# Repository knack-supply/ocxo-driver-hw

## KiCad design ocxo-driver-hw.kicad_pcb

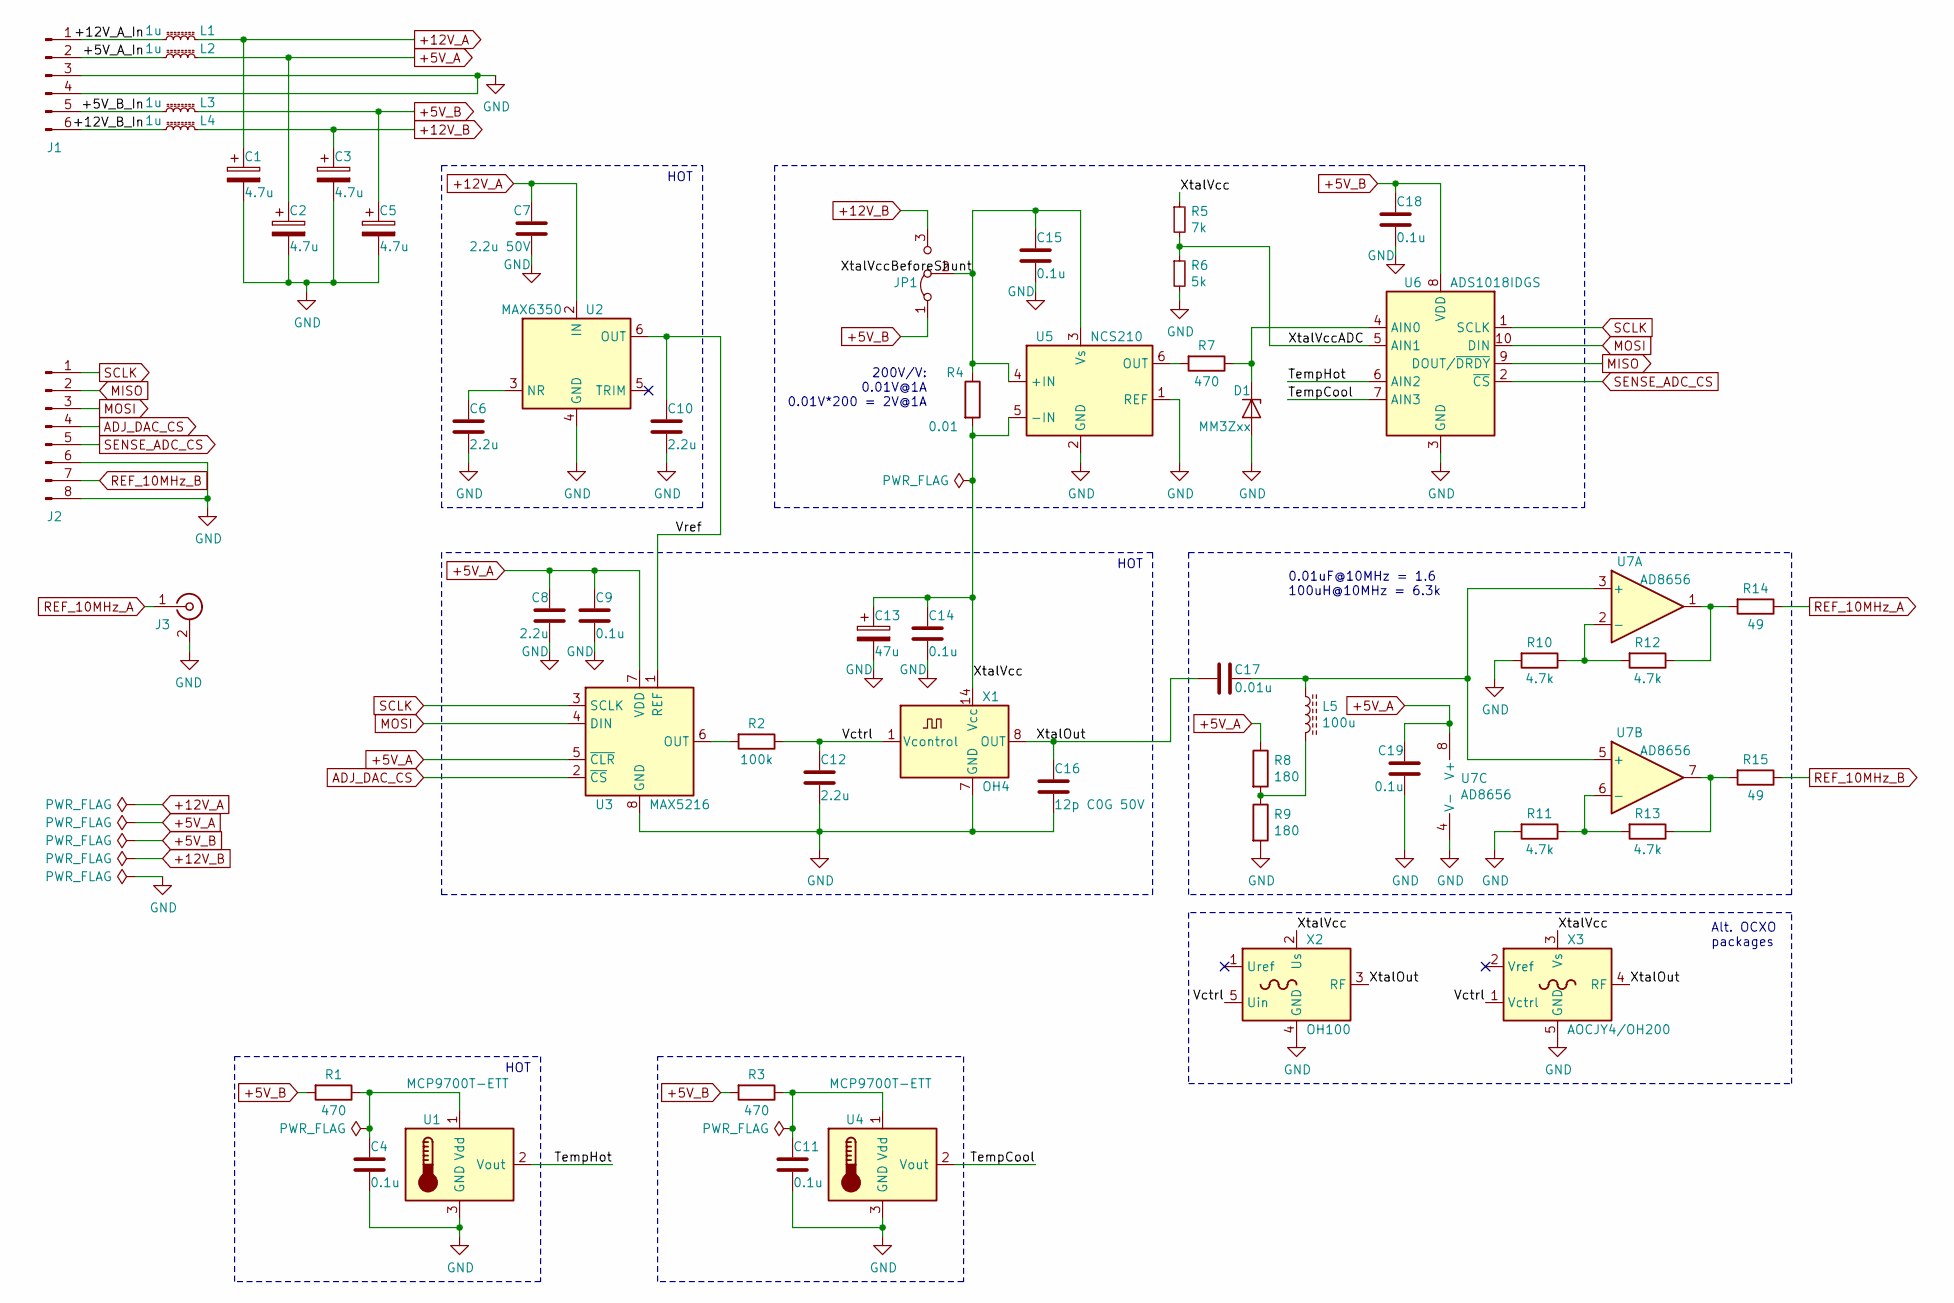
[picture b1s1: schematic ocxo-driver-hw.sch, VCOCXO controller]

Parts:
C1, C2, C3, C5: 4.7u; C_1206_3216Metric_Pad1.42x1.75mm_HandSolder
C4, C9, C11, C14, C15, C18, C19: 0.1u; C_0603_1608Metric_Pad1.05x0.95mm_HandSolder
C6, C8, C10: 2.2u; C_1206_3216Metric_Pad1.42x1.75mm_HandSolder
C7: 2.2u 50V; C_1206_3216Metric_Pad1.42x1.75mm_HandSolder
C12: 2.2u; C_0603_1608Metric_Pad1.05x0.95mm_HandSolder
C13: 47u; C_2816_7142Metric_Pad3.20x4.45mm_HandSolder
C16: 12p C0G 50V; C_0603_1608Metric_Pad1.05x0.95mm_HandSolder
C17: 0.01u; C_0603_1608Metric_Pad1.05x0.95mm_HandSolder
D1: MM3Zxx; D_SOD-123F
J1: Conn_01x06_Male; PinHeader_1x06_P2.54mm_Vertical
J2: Conn_01x08_Male; PinHeader_1x08_P2.54mm_Vertical
J3: Conn_Coaxial; MMCX_Molex_73415-1471_Vertical
JP1: Jumper_3_Bridged12; SolderJumper-3_P2.0mm_Open_TrianglePad1.0x1.5mm
L1, L2, L3, L4: 1u; L_1210_3225Metric_Pad1.42x2.65mm_HandSolder
L5: 100u; L_0805_2012Metric_Pad1.15x1.40mm_HandSolder
R1, R3, R7: 470; R_0603_1608Metric_Pad1.05x0.95mm_HandSolder
R2: 100k; R_0603_1608Metric_Pad1.05x0.95mm_HandSolder
R4: 0.01; R_0603_1608Metric_Pad1.05x0.95mm_HandSolder
R5: 7k; R_0603_1608Metric_Pad1.05x0.95mm_HandSolder
R6: 5k; R_0603_1608Metric_Pad1.05x0.95mm_HandSolder
R8, R9: 180; R_0603_1608Metric_Pad1.05x0.95mm_HandSolder
R10, R11, R12, R13: 4.7k; R_0603_1608Metric_Pad1.05x0.95mm_HandSolder
R14, R15: 49; R_0603_1608Metric_Pad1.05x0.95mm_HandSolder
U1, U4: MCP9700T-ETT; SOT-23
U2: MAX6350; SOIC-8_3.9x4.9mm_P1.27mm
U3: MAX5216; MSOP-8_3x3mm_P0.65mm
U5: NCS210; SOT-363_SC-70-6
U6: ADS1018IDGS; VSSOP-10_3x3mm_P0.5mm
U7: AD8656; SOIC-8_3.9x4.9mm_P1.27mm
X1: OH4; Oscillator_DIP-14
X2: OH100; Oscillator_OCXO_Morion_MV317
X3: AOCJY4/OH200; Oscillator_OCXO_Abracon_AOCJY4

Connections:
+5V_A: C2.1, C8.1, C9.1, C19.1, L2.2, R8.1, U3.5 (~CLR), U3.7 (VDD), U7.8 (V+)
+5V_B: C5.1, C18.1, JP1.1 (A), L3.2, R1.2, R3.2, U6.8 (VDD)
+12V_A: C1.1, C7.1, L1.2, U2.2 (IN)
+12V_B: C3.1, JP1.3 (B), L4.2
/+5V_A_In: J1.2, L2.1
/+5V_B_In: J1.5, L3.1
/+12V_A_In: J1.1, L1.1
/+12V_B_In: J1.6, L4.1
/TempCool: U4.2 (Vout), U6.7 (AIN3)
/TempHot: U1.2 (Vout), U6.6 (AIN2)
/Vctrl: C12.1, R2.1, X1.1 (Vcontrol), X2.5 (Uin), X3.1 (Vctrl)
/Vref: C10.1, U2.6 (OUT), U3.1 (REF)
/XtalOut: C16.1, C17.2, X1.8 (OUT), X2.3 (RF), X3.4 (RF)
/XtalVcc: C13.1, C14.1, R4.2, R5.1, U5.5 (-IN), X1.14 (Vcc), X2.2 (Us), X3.3 (Vs)
/XtalVccADC: R5.2, R6.1, U6.5 (AIN1)
/XtalVccBeforeShunt: C15.1, JP1.2 (C), R4.1, U5.3 (Vs), U5.4 (+IN)
ADJ_DAC_CS: J2.4, U3.2 (~CS)
GND: C1.2, C2.2, C3.2, C4.2, C5.2, C6.2, C7.2, C8.2, C9.2, C10.2, C11.2, C12.2, C13.2, C14.2, C15.2, C16.2, C18.2, C19.2, D1.2 (A), J1.3, J1.4, J2.6, J2.8, J3.2 (Ext), R6.2, R9.2, R10.2, R11.2, U1.3 (GND), U2.4 (GND), U3.8 (GND), U4.3 (GND), U5.1 (REF), U5.2 (GND), U6.3 (GND), U7.4 (V-), X1.7 (GND), X2.4 (GND), X3.5 (GND)
MISO: J2.2, U6.9 (DOUT/~DRDY)
MOSI: J2.3, U3.4 (DIN), U6.10 (DIN)
unnamed: C4.1, R1.1, U1.1 (Vdd)
unnamed: C6.1, U2.3 (NR)
unnamed: C11.1, R3.1, U4.1 (Vdd)
unnamed: C17.1, L5.1, U7.3 (+), U7.5 (+)
unnamed: D1.1 (K), R7.1, U6.4 (AIN0)
unnamed: L5.2, R8.2, R9.1
unnamed: R2.2, U3.6 (OUT)
unnamed: R7.2, U5.6 (OUT)
unnamed: R10.1, R12.2, U7.2 (-)
unnamed: R11.1, R13.2, U7.6 (-)
unnamed: R12.1, R14.2, U7.1
unnamed: R13.1, R15.2, U7.7
REF_10MHz_A: J3.1 (In), R14.1
REF_10MHz_B: J2.7, R15.1
SCLK: J2.1, U3.3 (SCLK), U6.1 (SCLK)
SENSE_ADC_CS: J2.5, U6.2 (~CS)

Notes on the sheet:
200V/V: 0.01V@1A 0.01V*200 = 2V@1A
HOT
0.01uF@10MHz = 1.6 100uH@10MHz = 6.3k
Alt. OCXO packages

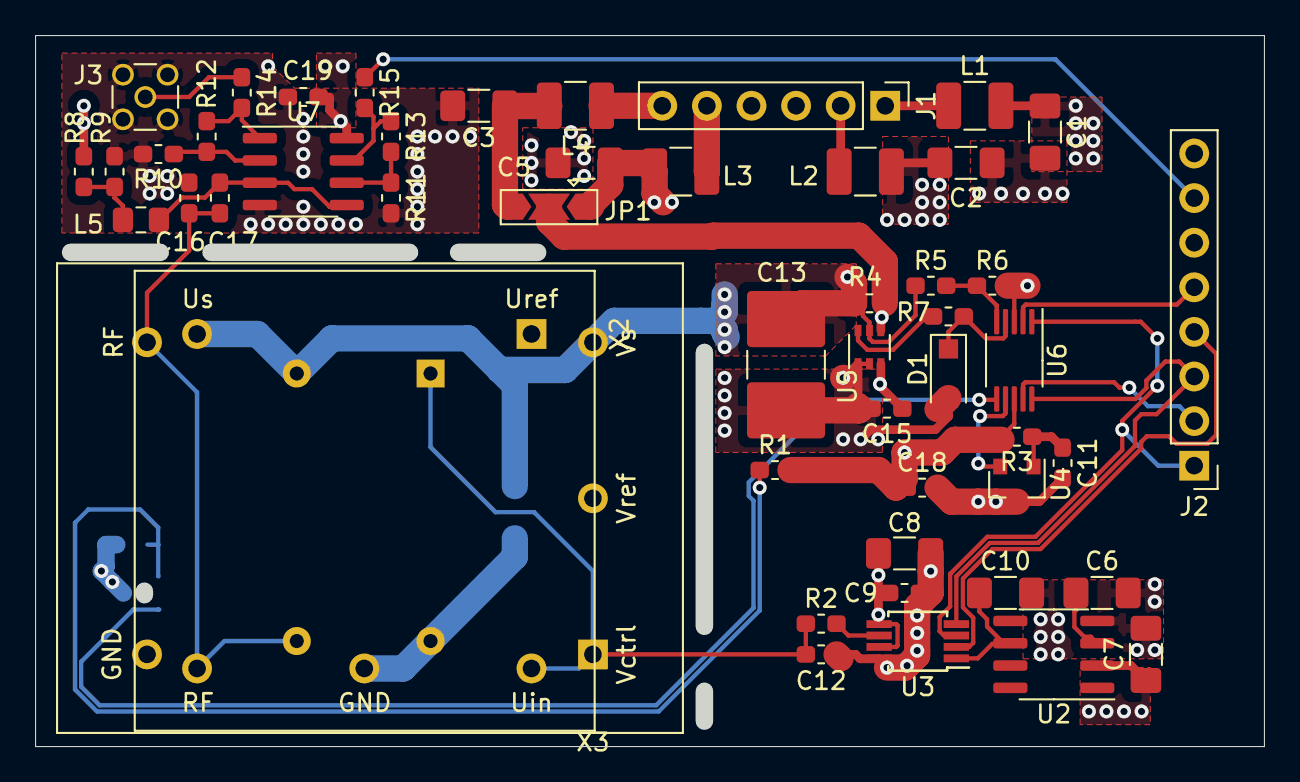
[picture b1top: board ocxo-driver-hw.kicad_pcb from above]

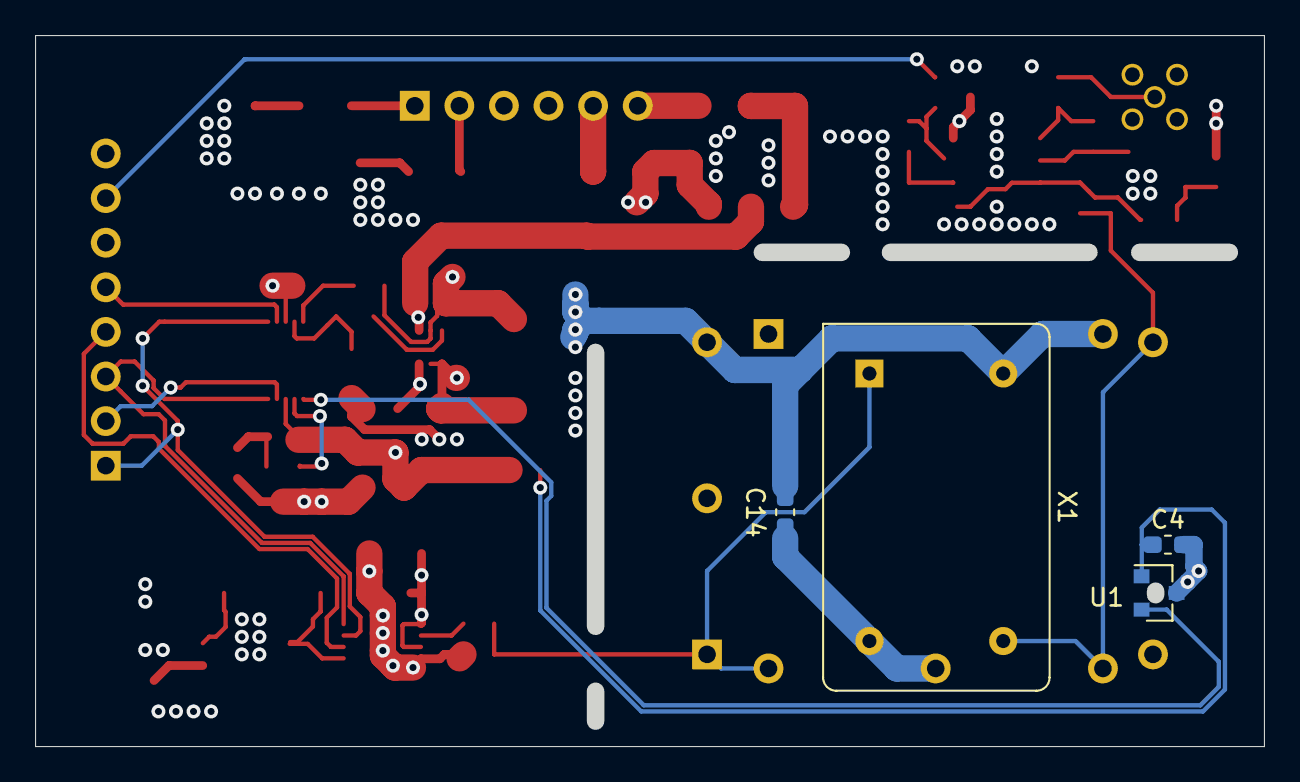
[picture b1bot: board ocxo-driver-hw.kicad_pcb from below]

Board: 4 copper layers, 69.1 x 39.6 mm, 54 parts (4 on the bottom side), 36 nets.

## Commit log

2019-06-20 initial version
